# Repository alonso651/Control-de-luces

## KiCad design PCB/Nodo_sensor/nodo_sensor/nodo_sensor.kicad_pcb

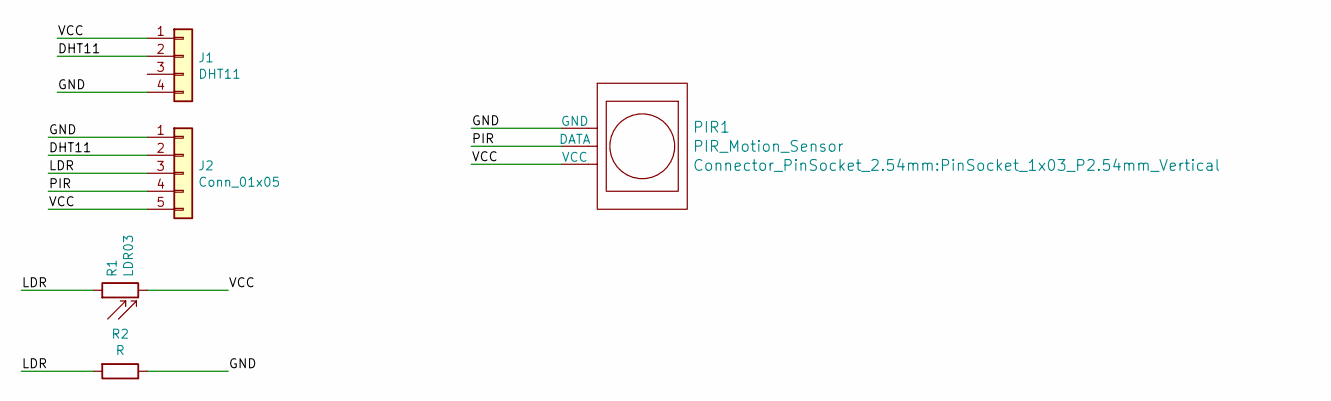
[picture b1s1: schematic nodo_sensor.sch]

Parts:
J1: DHT11; PinSocket_1x04_P2.54mm_Vertical
J2: Conn_01x05; PinSocket_1x05_P2.54mm_Vertical
PIR1: PIR_Motion_Sensor; PinSocket_1x03_P2.54mm_Vertical
R1: LDR03; R_LDR_10x8.5mm_P7.6mm_Vertical
R2: R

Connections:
/DHT11: J1.2, J2.2
/GND: J1.4, J2.1, PIR1.1 (GND), R2.1
/LDR: J2.3, R1.1, R2.2
/PIR: J2.4, PIR1.2 (DATA)
/VCC: J1.1, J2.5, PIR1.3 (VCC), R1.2

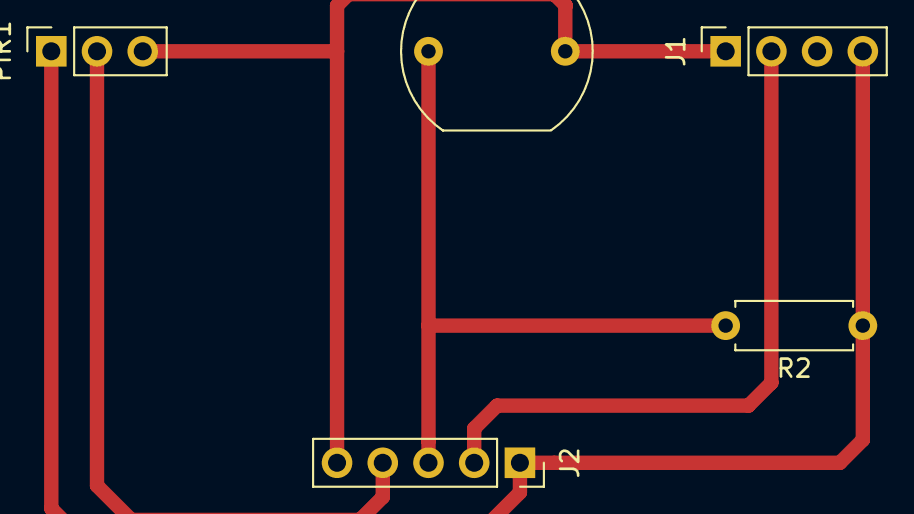
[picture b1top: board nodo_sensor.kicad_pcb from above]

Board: 2 copper layers, 5 parts (0 on the bottom side), 5 nets.

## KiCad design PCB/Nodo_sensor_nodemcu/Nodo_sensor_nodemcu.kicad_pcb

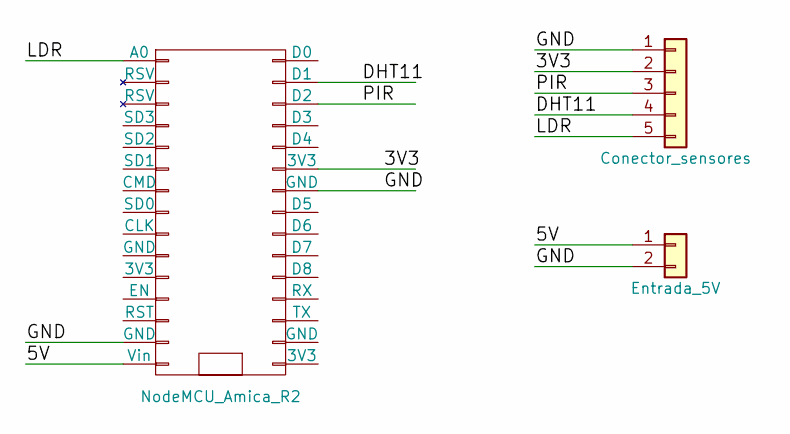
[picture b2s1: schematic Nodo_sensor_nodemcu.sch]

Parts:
Conector_sensores1: Conector_sensores; PinSocket_1x05_P2.54mm_Vertical
Entrada_5V1: Entrada_5V; TerminalBlock_bornier-2_P5.08mm
NodeMCU_V2: NodeMCU_Amica_R2

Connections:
/3V3: Conector_sensores1.2, NodeMCU_V2.25 (3V3)
/5V: Entrada_5V1.1, NodeMCU_V2.15 (Vin)
/DHT11: Conector_sensores1.4, NodeMCU_V2.29 (D1)
/GND: Conector_sensores1.1, Entrada_5V1.2, NodeMCU_V2.14 (GND), NodeMCU_V2.24 (GND)
/LDR: Conector_sensores1.5, NodeMCU_V2.1 (A0)
/PIR: Conector_sensores1.3, NodeMCU_V2.28 (D2)

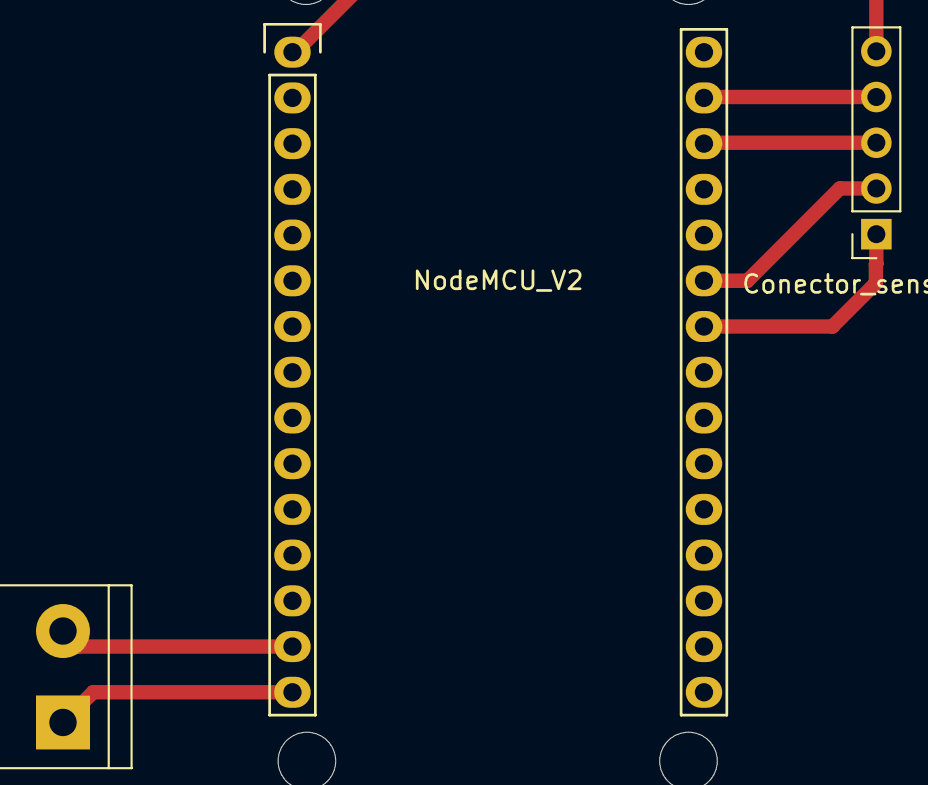
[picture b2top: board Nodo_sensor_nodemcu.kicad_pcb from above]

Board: 2 copper layers, 3 parts (0 on the bottom side), 6 nets.

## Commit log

2019-05-06 Funciona
2019-05-06 Versión 1
2019-05-06 PCBs Kicad
2019-05-07 V1.1 - 6 salidas
    Control para 6 salidas de relés y 6 interruptores
2019-05-07 PCB 6 RELES - 6 LLAVES
2019-05-10 nodo actuador
    cambio de pines para facilitar el diseño del PCB
